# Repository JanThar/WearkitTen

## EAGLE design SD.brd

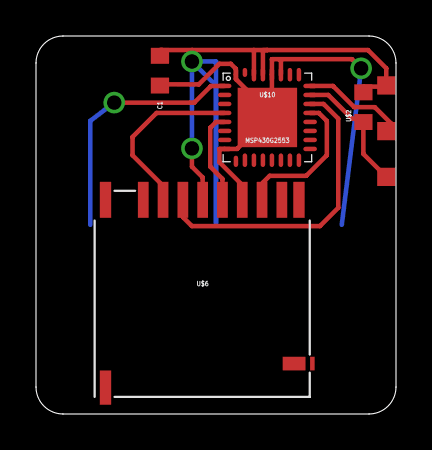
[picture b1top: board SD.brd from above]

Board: 2 copper layers, 20.0 x 21.0 mm, 5 parts (0 on the bottom side), 9 nets.

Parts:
C1: 100n; 603
U$1: CARRIER_SMD2SMD2_3POL_W; CARRIER_SMD2_WIDE_3POL
U$2: 10k; 603
U$6: MICRO-SD; SD-CARD-AMP
U$10: MSP430G2553; QFN32

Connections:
GND: C1.2, U$1.GND, U$6.GND, U$10.8, U$10.27, U$10.28, U$10.32, U$10.TP
unnamed: U$1.TST, U$10.24
unnamed: U$1.RST, U$2.1, U$10.23
unnamed: U$6.CLK, U$10.5
unnamed: U$6.CMD, U$10.22
unnamed: U$1.RX/TX, U$10.1
unnamed: U$6.DAT0, U$10.21
unnamed: U$6.CD/DAT3, U$10.4
VCC: C1.1, U$1.VCC, U$1.VCC'', U$2.2, U$6.VDD, U$10.29, U$10.30

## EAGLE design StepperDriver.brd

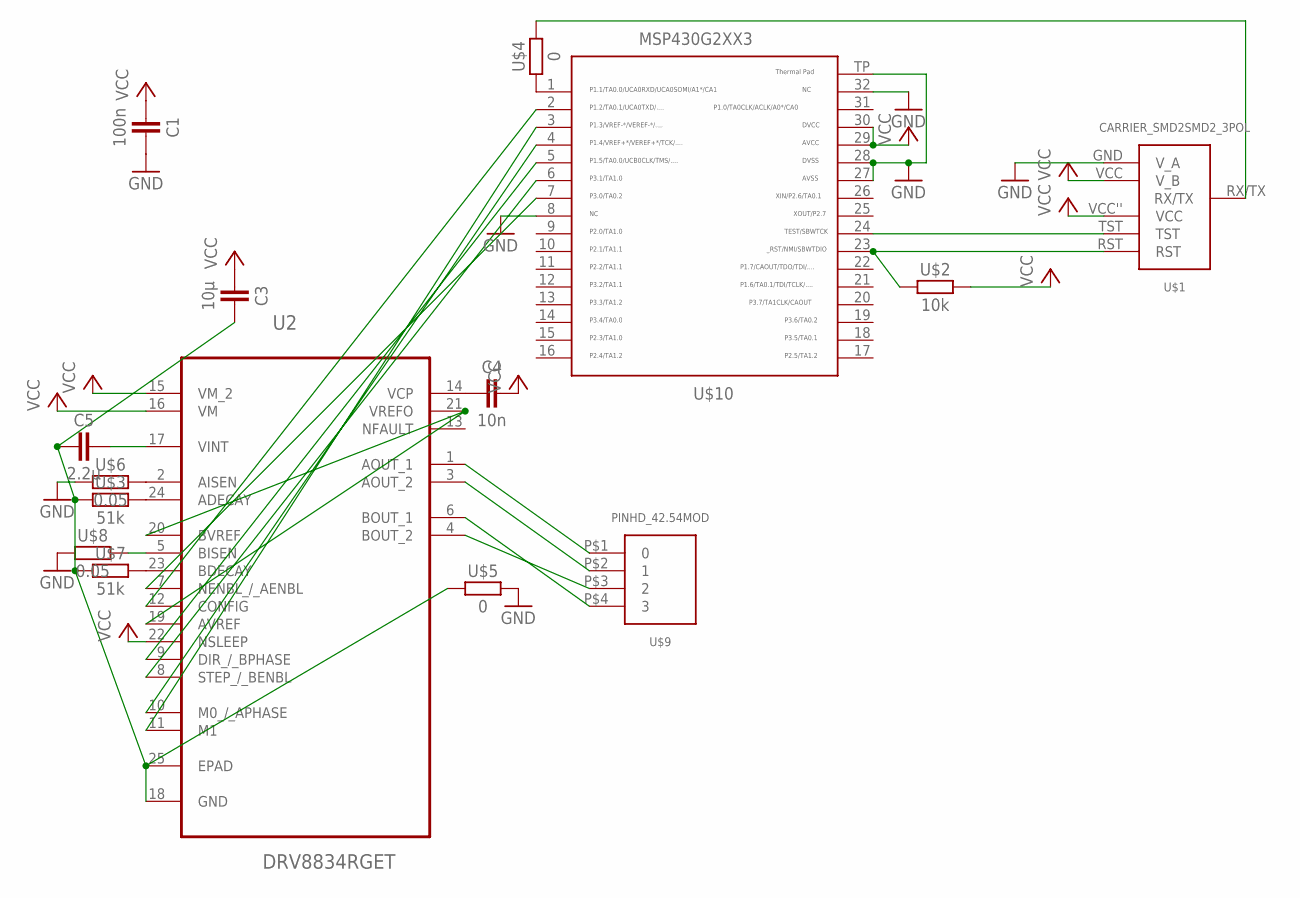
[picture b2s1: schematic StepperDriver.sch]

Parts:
C1: 100n; 603
C3: 10µ; 603
C4: 10n; 603
C5: 2.2µ; 603
U2: DRV8834RGET; QFN50P400X400X100-25N
U$1: CARRIER_SMD2SMD2_3POL; CARRIER_SMD2_3POL
U$2: 10k; 603
U$3, U$7: 51k; 603
U$4, U$5: 0; 603
U$6, U$8: 0.05; 603
U$9: PINHD_42.54MOD; PINHD_4_MOD
U$10: MSP430G2553; QFN32

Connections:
GND: C1.2, U$1.GND (V_A), U$5.2, U$6.1, U$8.1, U$10.8, U$10.27, U$10.28, U$10.32, U$10.TP
unnamed: C5.2, U2.17 (VINT)
unnamed: U$1.TST, U$10.24
unnamed: U$1.RST, U$2.1, U$10.23
unnamed: C4.1, U2.14 (VCP)
unnamed: U2.24 (ADECAY), U$3.2
unnamed: U2.23 (BDECAY), U$7.2
unnamed: U$4.1, U$10.1
unnamed: U$1.RX/TX, U$4.2
unnamed: U2.2 (AISEN), U$6.2
unnamed: U2.5 (BISEN), U$8.2
unnamed: U2.6 (BOUT_1), U$9.P$4 (3)
unnamed: U2.4 (BOUT_2), U$9.P$3 (2)
unnamed: C3.2, C5.1, U2.18 (GND), U2.25 (EPAD), U$3.1, U$5.1, U$7.1
unnamed: U2.1 (AOUT_1), U$9.P$1 (0)
unnamed: U2.3 (AOUT_2), U$9.P$2 (1)
unnamed: U2.19 (AVREF), U2.20 (BVREF), U2.21 (VREFO)
unnamed: U2.10 (M0_/_APHASE), U$10.4
unnamed: U2.11 (M1), U$10.3
unnamed: U2.7 (NENBL_/_AENBL), U$10.7
unnamed: U2.8 (STEP_/_BENBL), U$10.6
unnamed: U2.12 (CONFIG), U$10.2
unnamed: U2.9 (DIR_/_BPHASE), U$10.5
VCC: C1.1, C3.1, C4.2, U2.15 (VM_2), U2.16 (VM), U2.22 (NSLEEP), U$1.VCC (V_B), U$1.VCC'' (VCC), U$2.2, U$10.29, U$10.30

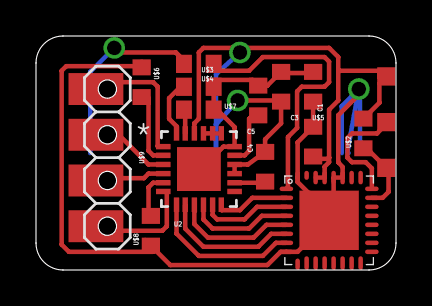
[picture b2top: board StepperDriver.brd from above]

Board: 2 copper layers, 20.0 x 13.0 mm, 15 parts (0 on the bottom side), 24 nets.
